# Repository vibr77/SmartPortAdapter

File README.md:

# SmartPortAdapter
 DB19 to IDC20 Adapter for IIc & IIGS

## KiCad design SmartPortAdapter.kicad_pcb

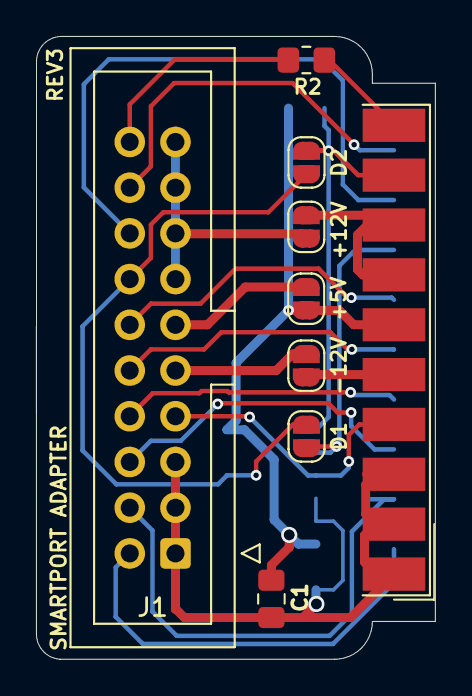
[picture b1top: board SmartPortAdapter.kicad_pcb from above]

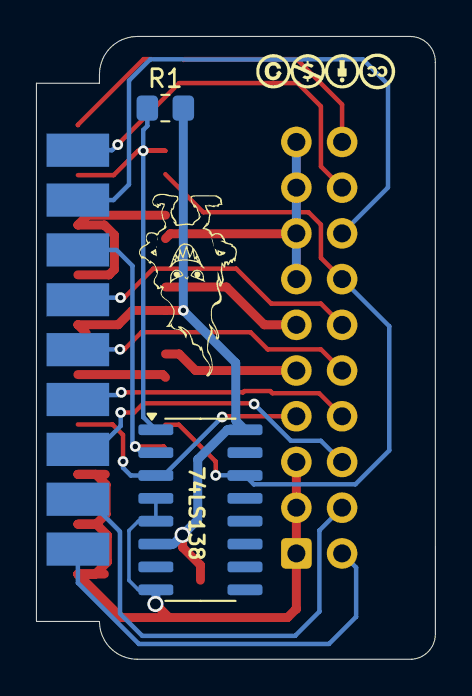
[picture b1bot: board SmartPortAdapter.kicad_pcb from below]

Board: 2 copper layers, 22.2 x 34.6 mm, 12 parts (3 on the bottom side), 21 nets.

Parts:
 : LOGO
+5V: +5V; SolderJumper-2_P1.3mm_Open_RoundedPad1.0x1.5mm
+12V: +12V; SolderJumper-2_P1.3mm_Open_RoundedPad1.0x1.5mm
-12V: -12V; SolderJumper-2_P1.3mm_Open_RoundedPad1.0x1.5mm
C1: 100nf; C_0805_2012Metric_Pad1.18x1.45mm_HandSolder
D1: D1; SolderJumper-2_P1.3mm_Open_RoundedPad1.0x1.5mm
D2: D2; SolderJumper-2_P1.3mm_Open_RoundedPad1.0x1.5mm
J1: APPLE_SDISKII; IDC-Header_2x10_P2.54mm_Vertical
R1: 10K; R_0805_2012Metric_Pad1.20x1.40mm_HandSolder
R2: 470; R_0805_2012Metric_Pad1.20x1.40mm_HandSolder
U1: DSUB-19-Edge
U2: 74HC138; SOIC-16_3.9x9.9mm_P1.27mm

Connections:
+12V: +12V.2 (B), U1.7, U1.8
+12V_D: +12V.1 (A), J1.13, J1.15, J1.17, J1.19
-12V: -12V.2 (B), U1.5
-12V_D: -12V.1 (A), J1.9
DEVICE_ENABLE: D1.2 (B), U1.17, U2.2 (A1)
DEVICE_ENABLE2: D2.2 (B), R1.1, U1.9, U2.1 (A0)
DEVICE_ENABLE_D: D1.1 (A), D2.1 (A), J1.14, U2.14 (~Y1)
EN35: J1.7, U1.4, U2.3 (A2)
GND: C1.2, J1.1, J1.3, J1.5, U1.1, U1.2, U1.3, U2.4 (~E0), U2.5 (~E1), U2.8 (GND)
RD_DATA: J1.16, U1.18
SEL: J1.12, U1.16
STEP0: J1.2, U1.11
STEP1: J1.4, U1.12
STEP2: J1.6, U1.13
STEP3: J1.8, U1.14
VCC: +5V.2 (B), C1.1, R1.2, U1.6, U2.6 (E2), U2.16 (VCC)
VCC_D: +5V.1 (A), J1.11
WR_DATA: J1.18, U1.19
WR_PROTECT: R2.2, U1.10
WR_PROTECT_D: J1.20, R2.1
WR_REQ: J1.10, U1.15

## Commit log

2025-05-05 rev3 IIGS ROM3
